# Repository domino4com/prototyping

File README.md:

# Prototype Boards

## Boards

| Board | Size | Design | Description |
|--|:--:|:--:|--|
| IPB | 1U |||
| IPP | 2x3U |||
| EPA | EXT || Analog sensor board |
| EPB | EXT || Bus board |

## Size
### Standard Boards
All standard boards are a multiple of 32x32 mm, called 1U (It comes from Lego, where one dot is 8x8mm).
In order to add two boards together, 0.1 mm is subtracted from each side (also a Lego standard).
So a single chip is 31.8x31.8 mm and a large 2x3 chip (2x3U) board is (2x32-0.1-0.1) x (3x32-0.1-0.1) 63.8x95.8mm
All boards are standard 1.6mm thick.
The rest you can deduct from the design.

### Extension boards (EXT)
No specific size requirements, but I try to keep the width within 31.8mm.
> NOTE: The boards are only 1mm thick!!!

## Eagle 
All boards are designed in Eagle, which you can [freely download](https://www.autodesk.com/products/eagle/free-download).

In Eagle there is an ULP, that allows you to make a library from the schematic/layout.

# License: 

Creative Commons Attribution-NonCommercial-ShareAlike 4.0 International Public License

[View License Deed](https://creativecommons.org/licenses/by-nc-sa/4.0/) | [View Legal Code](https://creativecommons.org/licenses/by-nc-sa/4.0/legalcode)

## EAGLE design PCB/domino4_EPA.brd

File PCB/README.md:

# Eagle files

## Boards

| Board | Size | Design | Description |
|--|:--:|:--:|--|
| IPB | 1U |||
| IPP | 2x3U |||
| EPA | EXT || Analog sensor board |
| EPB | EXT || Bus board |

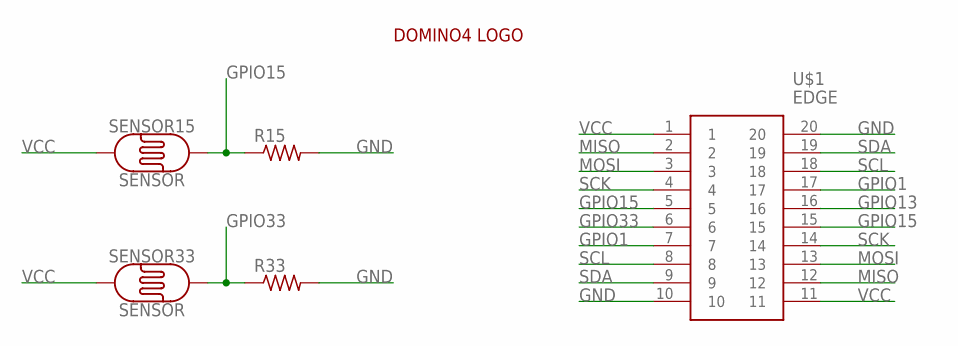
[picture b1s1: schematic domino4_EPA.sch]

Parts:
R15, R33: R-US_FLIPFLOP; 0805-THM
SENSOR15, SENSOR33: SENSOR; PHOTOCELL-KIT
U$1: EDGE
U$5: DOMINO4_LOGO

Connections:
GND: R15.2, R33.2, U$1.10, U$1.20
GPIO1: U$1.7, U$1.17
GPIO13: U$1.16
GPIO15: R15.1, SENSOR15.2, U$1.5, U$1.15
GPIO33: R33.1, SENSOR33.2, U$1.6
MISO: U$1.2, U$1.12
MOSI: U$1.3, U$1.13
SCK: U$1.4, U$1.14
SCL: U$1.8, U$1.18
SDA: U$1.9, U$1.19
VCC: SENSOR15.1, SENSOR33.1, U$1.1, U$1.11

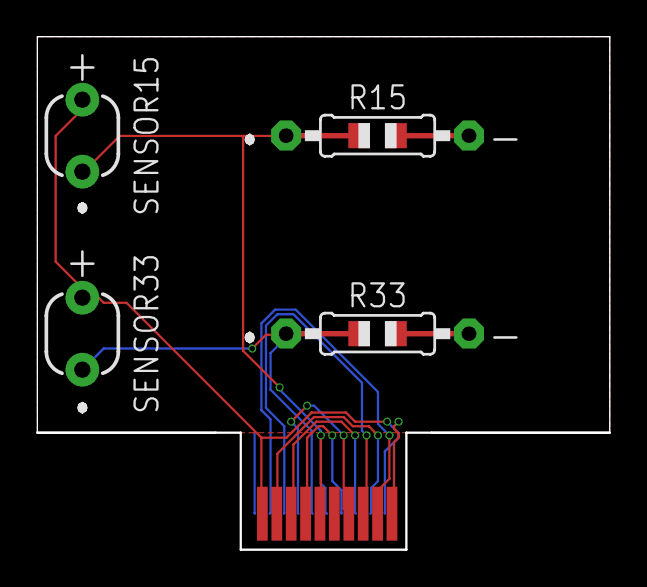
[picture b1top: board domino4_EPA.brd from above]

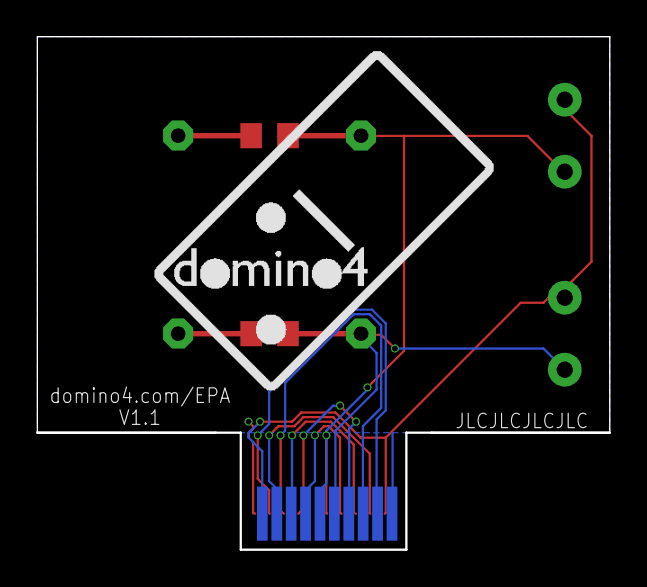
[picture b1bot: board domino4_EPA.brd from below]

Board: 2 copper layers, 31.8 x 28.5 mm, 7 parts (2 on the bottom side), 10 nets.

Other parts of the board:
U$3: JLCPCB-ORDER-NO

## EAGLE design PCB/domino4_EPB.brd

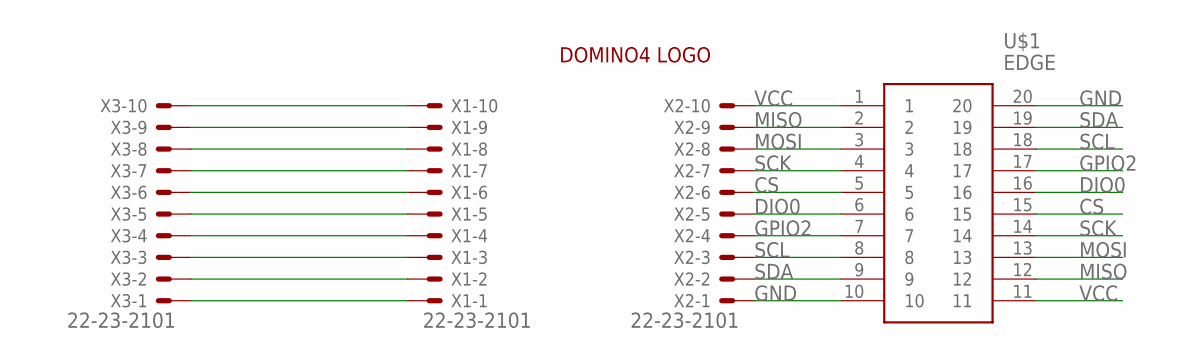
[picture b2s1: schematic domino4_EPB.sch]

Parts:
U$1: EDGE
U$2: DOMINO4_LOGO
X1, X2, X3: 22-23-2101

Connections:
CS: U$1.5, U$1.15, X2.6
DIO0: U$1.6, U$1.16, X2.5
GND: U$1.10, U$1.20, X2.1
GPIO2: U$1.7, U$1.17, X2.4
MISO: U$1.2, U$1.12, X2.9
MOSI: U$1.3, U$1.13, X2.8
unnamed: X1.10, X3.10
unnamed: X1.9, X3.9
unnamed: X1.8, X3.8
unnamed: X1.7, X3.7
unnamed: X1.6, X3.6
unnamed: X1.5, X3.5
unnamed: X1.4, X3.4
unnamed: X1.3, X3.3
unnamed: X1.2, X3.2
unnamed: X1.1, X3.1
SCK: U$1.4, U$1.14, X2.7
SCL: U$1.8, U$1.18, X2.3
SDA: U$1.9, U$1.19, X2.2
VCC: U$1.1, U$1.11, X2.10

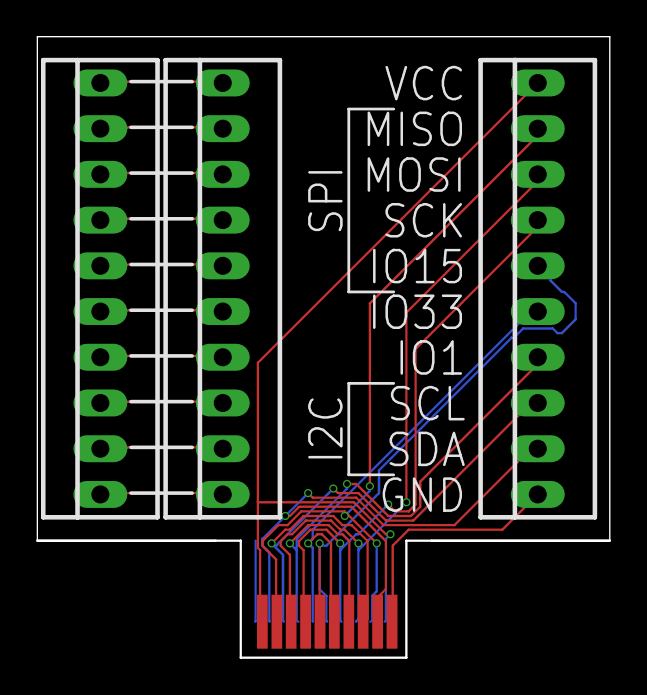
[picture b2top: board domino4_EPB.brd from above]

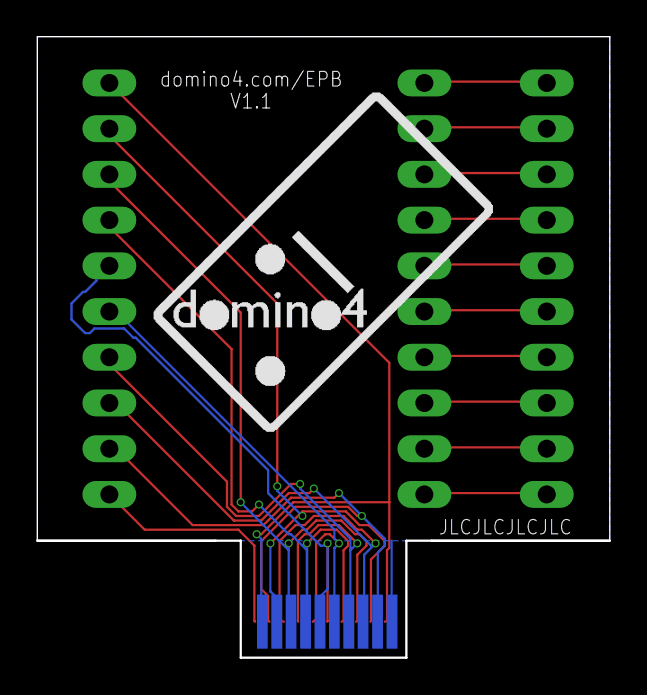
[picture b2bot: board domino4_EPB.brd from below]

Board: 2 copper layers, 31.8 x 34.5 mm, 6 parts (2 on the bottom side), 20 nets.

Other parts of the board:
U$3: JLCPCB-ORDER-NO

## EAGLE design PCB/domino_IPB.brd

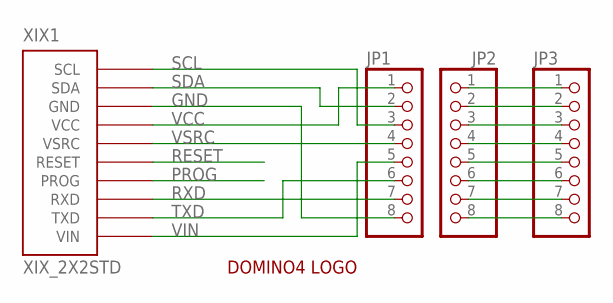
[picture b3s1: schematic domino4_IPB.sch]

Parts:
JP1, JP2, JP3: PINHD-1X8; 1X08
U$1: DOMINO4_LOGOHALF; DOMINO4_LOGO_HALF
XIX1: XIX_2X2STD; XIX_2X2

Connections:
GND: JP1.8, XIX1.GND@1 (GND), XIX1.GND@2 (GND), XIX1.GND@3 (GND), XIX1.GND@4 (GND)
unnamed: JP2.1, JP3.1
unnamed: JP2.2, JP3.2
unnamed: JP2.3, JP3.3
unnamed: JP2.4, JP3.4
unnamed: JP2.5, JP3.5
unnamed: JP2.6, JP3.6
unnamed: JP2.7, JP3.7
unnamed: JP2.8, JP3.8
PROG: XIX1.PROG@5 (PROG), XIX1.PROG@6 (PROG), XIX1.PROG@7 (PROG), XIX1.PROG@8 (PROG)
RESET: XIX1.RESET@5 (RESET), XIX1.RESET@6 (RESET), XIX1.RESET@7 (RESET), XIX1.RESET@8 (RESET)
RXD: JP1.7, XIX1.RXD@5 (RXD), XIX1.RXD@6 (RXD), XIX1.RXD@7 (RXD), XIX1.RXD@8 (RXD)
SCL: JP1.3, XIX1.SCL@1 (SCL), XIX1.SCL@2 (SCL), XIX1.SCL@3 (SCL), XIX1.SCL@4 (SCL)
SDA: JP1.2, XIX1.SDA@1 (SDA), XIX1.SDA@2 (SDA), XIX1.SDA@3 (SDA), XIX1.SDA@4 (SDA)
TXD: JP1.6, XIX1.TXD@5 (TXD), XIX1.TXD@6 (TXD), XIX1.TXD@7 (TXD), XIX1.TXD@8 (TXD)
VCC: JP1.1, XIX1.VCC@1 (VCC), XIX1.VCC@2 (VCC), XIX1.VCC@3 (VCC), XIX1.VCC@4 (VCC)
VIN: JP1.5, XIX1.VIN@5 (VIN), XIX1.VIN@6 (VIN), XIX1.VIN@7 (VIN), XIX1.VIN@8 (VIN)
VSRC: JP1.4, XIX1.VSRC@1 (VSRC), XIX1.VSRC@2 (VSRC), XIX1.VSRC@3 (VSRC), XIX1.VSRC@4 (VSRC)

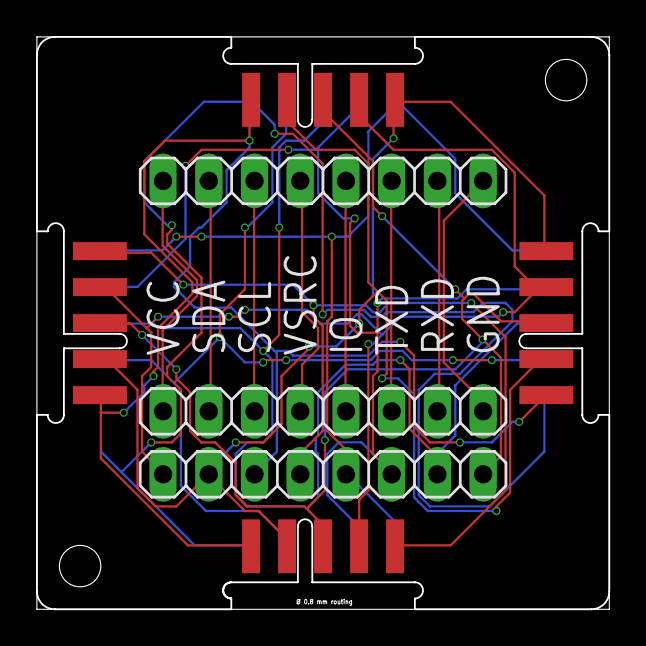
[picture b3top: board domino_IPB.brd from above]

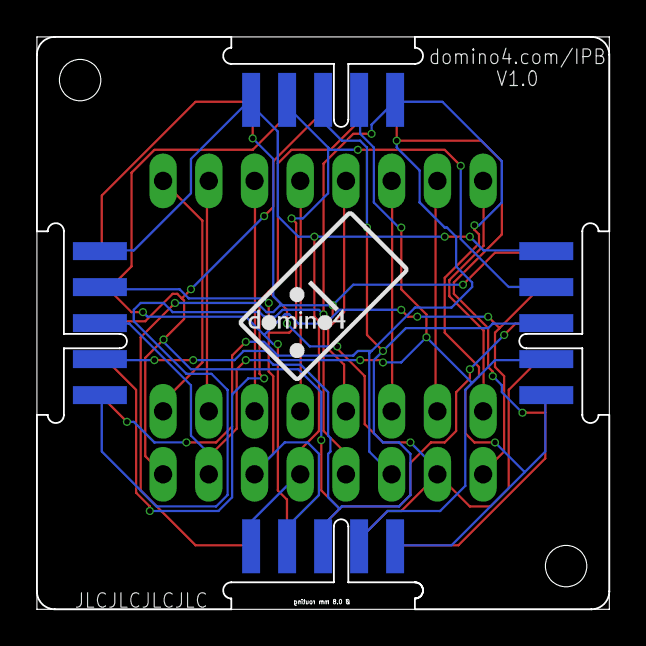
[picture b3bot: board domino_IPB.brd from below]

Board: 2 copper layers, 31.8 x 31.8 mm, 6 parts (2 on the bottom side), 18 nets.

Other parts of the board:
U$3: JLCPCB-ORDER-NO

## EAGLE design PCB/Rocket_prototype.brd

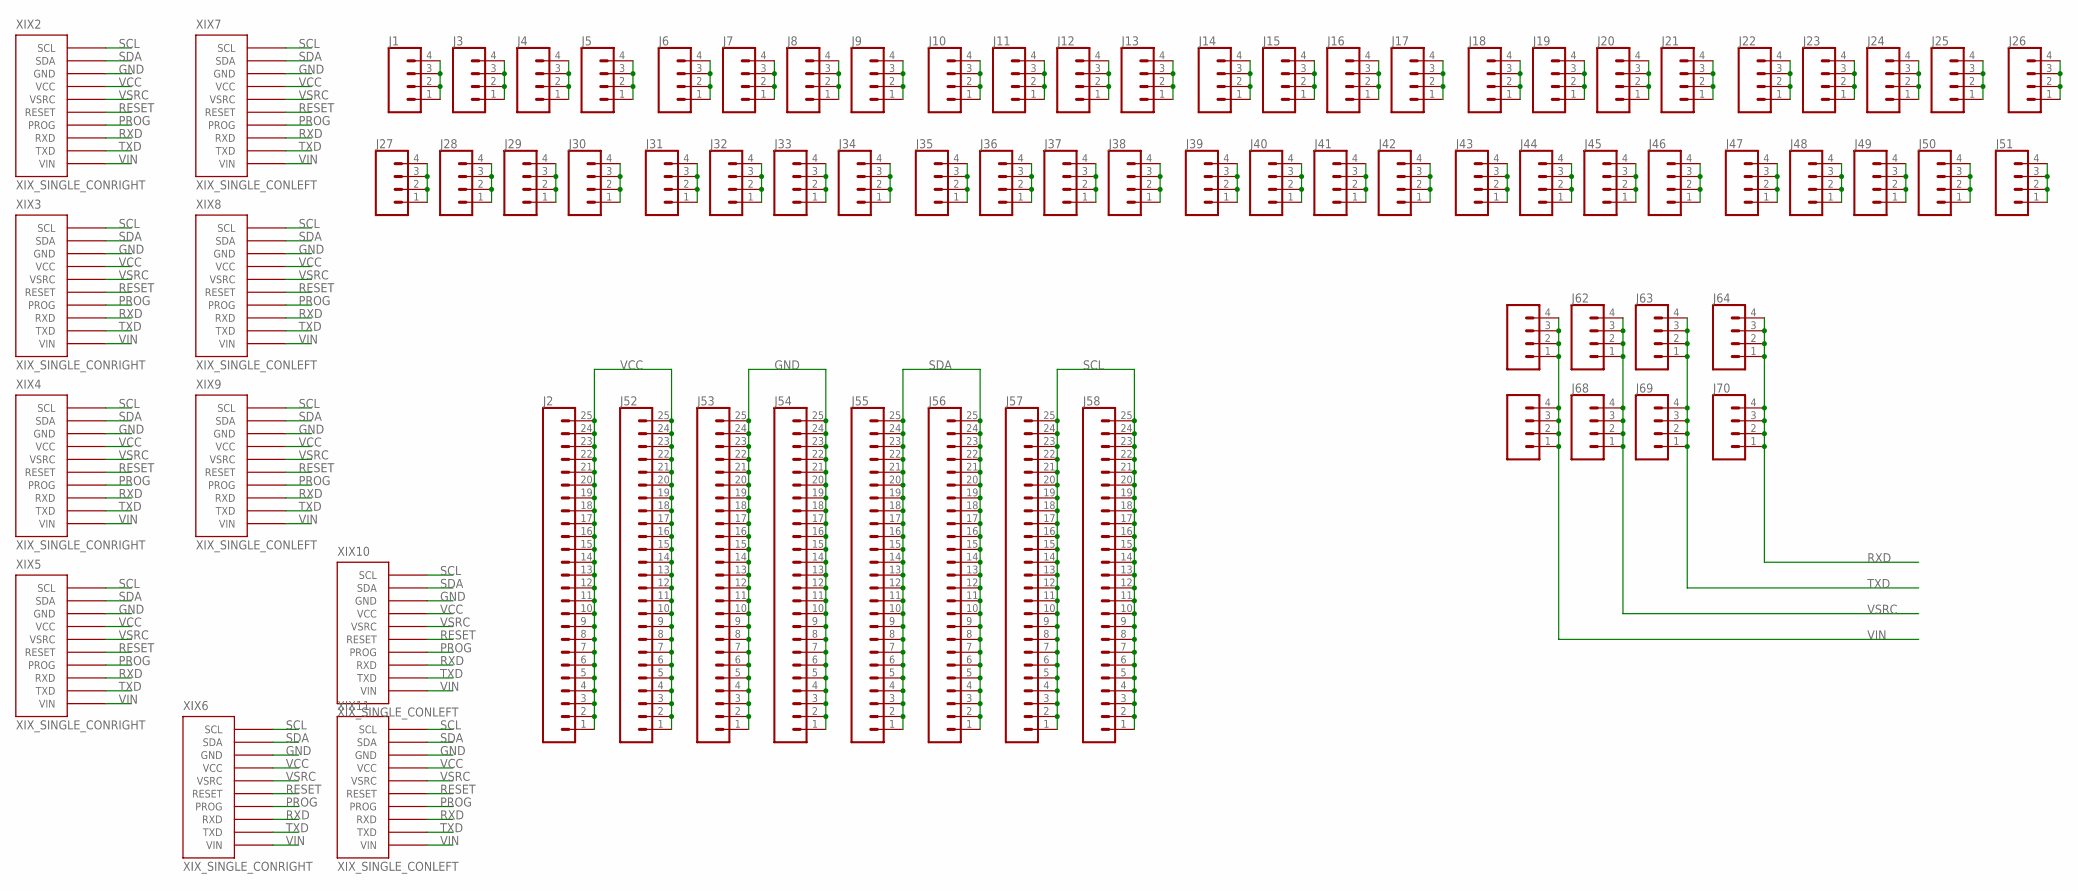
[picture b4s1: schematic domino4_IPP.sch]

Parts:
J1, J3, J4, J5, J6, J7, J8, J9, J10, J11, J12, J13, J14, J15, J16, J17, J18, J19, J20, J21, J22, J23, J24, J25, J26, J27, J28, J29, J30, J31, J32, J33, J34, J35, J36, J37, J38, J39, J40, J41, J42, J43, J44, J45, J46, J47, J48, J49, J50, J51, J61, J62, J63, J64, J67, J68, J69, J70: CONN_04PTH; 1X04
J2, J52, J53, J54, J55, J56, J57, J58: CONN_25; 1X25
XIX2, XIX3, XIX4, XIX5, XIX6: XIX_SINGLE_CONRIGHT; XIX_SINGLE_CON_RIGHT
XIX7, XIX8, XIX9, XIX10, XIX11: XIX_SINGLE_CONLEFT; XIX_SINGLE_CON_LEFT

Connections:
GND: J53.1, J53.2, J53.3, J53.4, J53.5, J53.6, J53.7, J53.8, J53.9, J53.10, J53.11, J53.12, J53.13, J53.14, J53.15, J53.16, J53.17, J53.18, J53.19, J53.20, J53.21, J53.22, J53.23, J53.24, J53.25, J54.1, J54.2, J54.3, J54.4, J54.5, J54.6, J54.7, J54.8, J54.9, J54.10, J54.11, J54.12, J54.13, J54.14, J54.15, J54.16, J54.17, J54.18, J54.19, J54.20, J54.21, J54.22, J54.23, J54.24, J54.25, XIX2.GND@4 (GND), XIX3.GND@4 (GND), XIX4.GND@4 (GND), XIX5.GND@4 (GND), XIX6.GND@4 (GND), XIX7.GND@1 (GND), XIX8.GND@1 (GND), XIX9.GND@1 (GND), XIX10.GND@1 (GND), XIX11.GND@1 (GND)
unnamed: J1.1, J1.2, J1.3, J1.4
unnamed: J3.1, J3.2, J3.3, J3.4
unnamed: J4.1, J4.2, J4.3, J4.4
unnamed: J5.1, J5.2, J5.3, J5.4
unnamed: J6.1, J6.2, J6.3, J6.4
unnamed: J7.1, J7.2, J7.3, J7.4
unnamed: J8.1, J8.2, J8.3, J8.4
unnamed: J9.1, J9.2, J9.3, J9.4
unnamed: J10.1, J10.2, J10.3, J10.4
unnamed: J11.1, J11.2, J11.3, J11.4
unnamed: J12.1, J12.2, J12.3, J12.4
unnamed: J13.1, J13.2, J13.3, J13.4
unnamed: J14.1, J14.2, J14.3, J14.4
unnamed: J15.1, J15.2, J15.3, J15.4
unnamed: J16.1, J16.2, J16.3, J16.4
unnamed: J17.1, J17.2, J17.3, J17.4
unnamed: J18.1, J18.2, J18.3, J18.4
unnamed: J19.1, J19.2, J19.3, J19.4
unnamed: J20.1, J20.2, J20.3, J20.4
unnamed: J21.1, J21.2, J21.3, J21.4
unnamed: J22.1, J22.2, J22.3, J22.4
unnamed: J23.1, J23.2, J23.3, J23.4
unnamed: J24.1, J24.2, J24.3, J24.4
unnamed: J25.1, J25.2, J25.3, J25.4
unnamed: J26.1, J26.2, J26.3, J26.4
unnamed: J27.1, J27.2, J27.3, J27.4
unnamed: J28.1, J28.2, J28.3, J28.4
unnamed: J29.1, J29.2, J29.3, J29.4
unnamed: J30.1, J30.2, J30.3, J30.4
unnamed: J31.1, J31.2, J31.3, J31.4
unnamed: J32.1, J32.2, J32.3, J32.4
unnamed: J33.1, J33.2, J33.3, J33.4
unnamed: J34.1, J34.2, J34.3, J34.4
unnamed: J35.1, J35.2, J35.3, J35.4
unnamed: J36.1, J36.2, J36.3, J36.4
unnamed: J37.1, J37.2, J37.3, J37.4
unnamed: J38.1, J38.2, J38.3, J38.4
unnamed: J39.1, J39.2, J39.3, J39.4
unnamed: J40.1, J40.2, J40.3, J40.4
unnamed: J41.1, J41.2, J41.3, J41.4
unnamed: J42.1, J42.2, J42.3, J42.4
unnamed: J43.1, J43.2, J43.3, J43.4
unnamed: J44.1, J44.2, J44.3, J44.4
unnamed: J45.1, J45.2, J45.3, J45.4
unnamed: J46.1, J46.2, J46.3, J46.4
unnamed: J47.1, J47.2, J47.3, J47.4
unnamed: J48.1, J48.2, J48.3, J48.4
unnamed: J49.1, J49.2, J49.3, J49.4
unnamed: J50.1, J50.2, J50.3, J50.4
unnamed: J51.1, J51.2, J51.3, J51.4
PROG: XIX2.PROG@8 (PROG), XIX3.PROG@8 (PROG), XIX4.PROG@8 (PROG), XIX5.PROG@8 (PROG), XIX6.PROG@8 (PROG), XIX7.PROG@2 (PROG), XIX8.PROG@2 (PROG), XIX9.PROG@2 (PROG), XIX10.PROG@2 (PROG), XIX11.PROG@2 (PROG)
RESET: XIX2.RESET@8 (RESET), XIX3.RESET@8 (RESET), XIX4.RESET@8 (RESET), XIX5.RESET@8 (RESET), XIX6.RESET@8 (RESET), XIX7.RESET@2 (RESET), XIX8.RESET@2 (RESET), XIX9.RESET@2 (RESET), XIX10.RESET@2 (RESET), XIX11.RESET@2 (RESET)
RXD: J64.1, J64.2, J64.3, J64.4, J70.1, J70.2, J70.3, J70.4, XIX2.RXD@8 (RXD), XIX3.RXD@8 (RXD), XIX4.RXD@8 (RXD), XIX5.RXD@8 (RXD), XIX6.RXD@8 (RXD), XIX7.RXD@2 (RXD), XIX8.RXD@2 (RXD), XIX9.RXD@2 (RXD), XIX10.RXD@2 (RXD), XIX11.RXD@2 (RXD)
SCL: J57.1, J57.2, J57.3, J57.4, J57.5, J57.6, J57.7, J57.8, J57.9, J57.10, J57.11, J57.12, J57.13, J57.14, J57.15, J57.16, J57.17, J57.18, J57.19, J57.20, J57.21, J57.22, J57.23, J57.24, J57.25, J58.1, J58.2, J58.3, J58.4, J58.5, J58.6, J58.7, J58.8, J58.9, J58.10, J58.11, J58.12, J58.13, J58.14, J58.15, J58.16, J58.17, J58.18, J58.19, J58.20, J58.21, J58.22, J58.23, J58.24, J58.25, XIX2.SCL@4 (SCL), XIX3.SCL@4 (SCL), XIX4.SCL@4 (SCL), XIX5.SCL@4 (SCL), XIX6.SCL@4 (SCL), XIX7.SCL@1 (SCL), XIX8.SCL@1 (SCL), XIX9.SCL@1 (SCL), XIX10.SCL@1 (SCL), XIX11.SCL@1 (SCL)
SDA: J55.1, J55.2, J55.3, J55.4, J55.5, J55.6, J55.7, J55.8, J55.9, J55.10, J55.11, J55.12, J55.13, J55.14, J55.15, J55.16, J55.17, J55.18, J55.19, J55.20, J55.21, J55.22, J55.23, J55.24, J55.25, J56.1, J56.2, J56.3, J56.4, J56.5, J56.6, J56.7, J56.8, J56.9, J56.10, J56.11, J56.12, J56.13, J56.14, J56.15, J56.16, J56.17, J56.18, J56.19, J56.20, J56.21, J56.22, J56.23, J56.24, J56.25, XIX2.SDA@4 (SDA), XIX3.SDA@4 (SDA), XIX4.SDA@4 (SDA), XIX5.SDA@4 (SDA), XIX6.SDA@4 (SDA), XIX7.SDA@1 (SDA), XIX8.SDA@1 (SDA), XIX9.SDA@1 (SDA), XIX10.SDA@1 (SDA), XIX11.SDA@1 (SDA)
TXD: J63.1, J63.2, J63.3, J63.4, J69.1, J69.2, J69.3, J69.4, XIX2.TXD@8 (TXD), XIX3.TXD@8 (TXD), XIX4.TXD@8 (TXD), XIX5.TXD@8 (TXD), XIX6.TXD@8 (TXD), XIX7.TXD@2 (TXD), XIX8.TXD@2 (TXD), XIX9.TXD@2 (TXD), XIX10.TXD@2 (TXD), XIX11.TXD@2 (TXD)
VCC: J2.1, J2.2, J2.3, J2.4, J2.5, J2.6, J2.7, J2.8, J2.9, J2.10, J2.11, J2.12, J2.13, J2.14, J2.15, J2.16, J2.17, J2.18, J2.19, J2.20, J2.21, J2.22, J2.23, J2.24, J2.25, J52.1, J52.2, J52.3, J52.4, J52.5, J52.6, J52.7, J52.8, J52.9, J52.10, J52.11, J52.12, J52.13, J52.14, J52.15, J52.16, J52.17, J52.18, J52.19, J52.20, J52.21, J52.22, J52.23, J52.24, J52.25, XIX2.VCC@4 (VCC), XIX3.VCC@4 (VCC), XIX4.VCC@4 (VCC), XIX5.VCC@4 (VCC), XIX6.VCC@4 (VCC), XIX7.VCC@1 (VCC), XIX8.VCC@1 (VCC), XIX9.VCC@1 (VCC), XIX10.VCC@1 (VCC), XIX11.VCC@1 (VCC)
VIN: J61.1, J61.2, J61.3, J61.4, J67.1, J67.2, J67.3, J67.4, XIX2.VRAW@8 (VIN), XIX3.VRAW@8 (VIN), XIX4.VRAW@8 (VIN), XIX5.VRAW@8 (VIN), XIX6.VRAW@8 (VIN), XIX7.VRAW@2 (VIN), XIX8.VRAW@2 (VIN), XIX9.VRAW@2 (VIN), XIX10.VRAW@2 (VIN), XIX11.VRAW@2 (VIN)
VSRC: J62.1, J62.2, J62.3, J62.4, J68.1, J68.2, J68.3, J68.4, XIX2.VBAT@4 (VSRC), XIX3.VBAT@4 (VSRC), XIX4.VBAT@4 (VSRC), XIX5.VBAT@4 (VSRC), XIX6.VBAT@4 (VSRC), XIX7.VBAT@1 (VSRC), XIX8.VBAT@1 (VSRC), XIX9.VBAT@1 (VSRC), XIX10.VBAT@1 (VSRC), XIX11.VBAT@1 (VSRC)

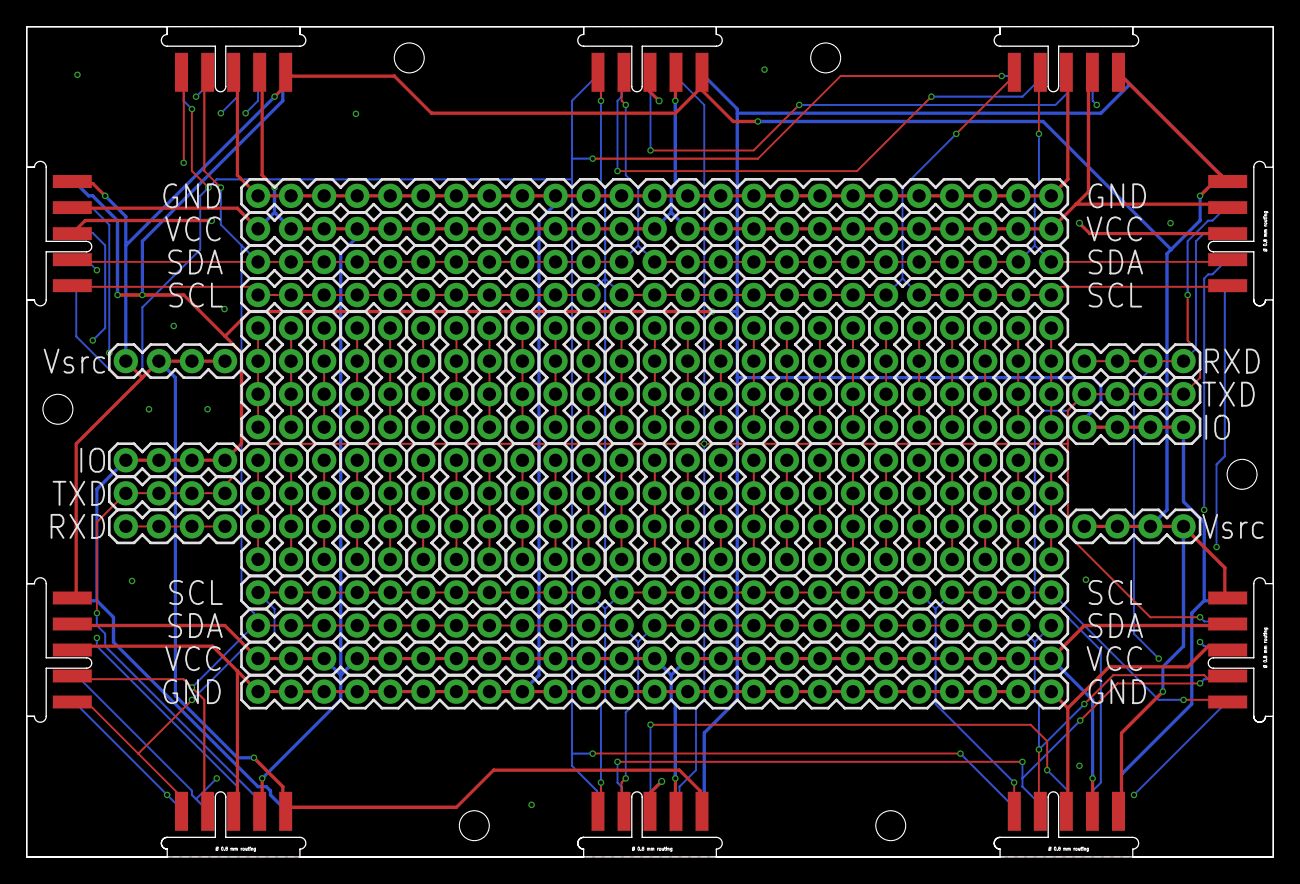
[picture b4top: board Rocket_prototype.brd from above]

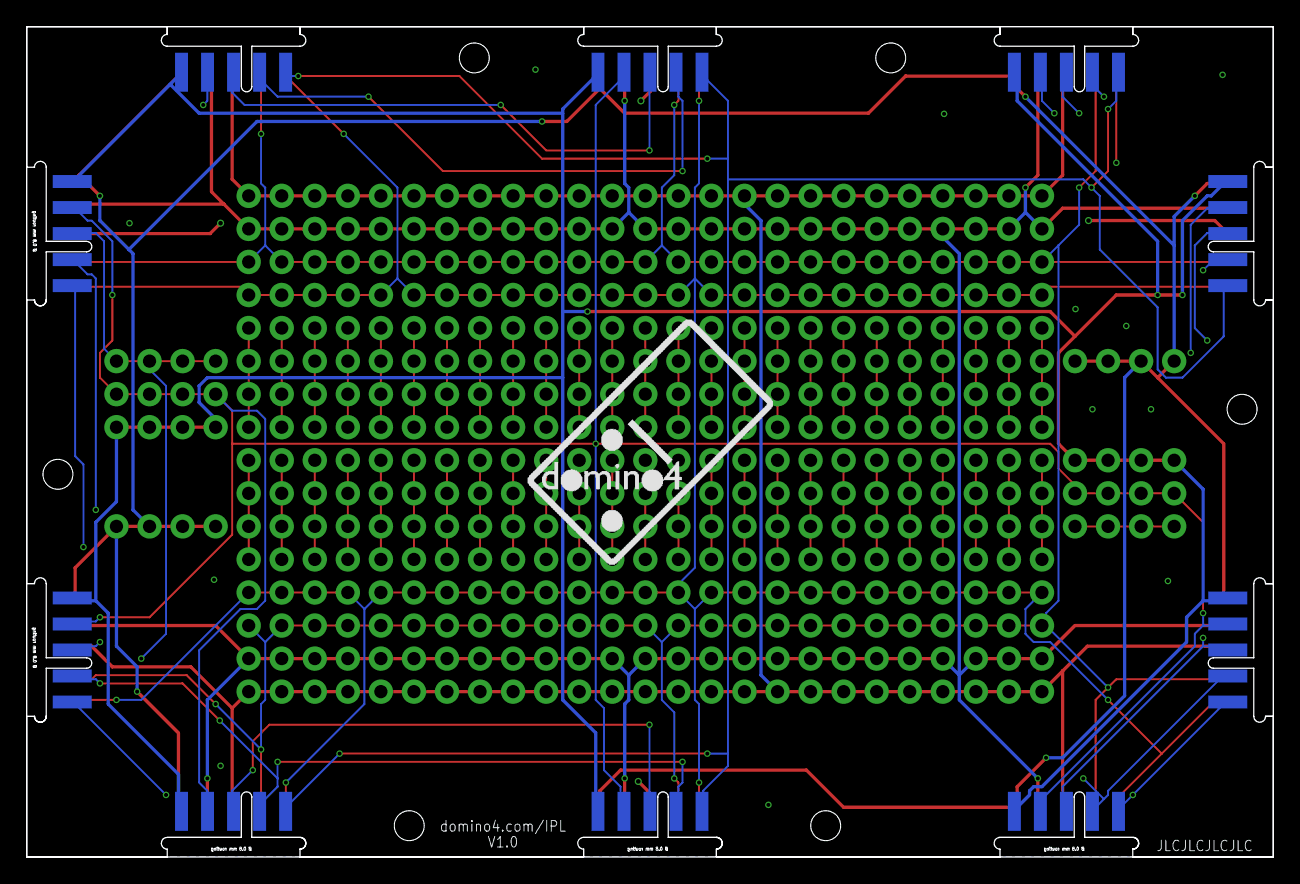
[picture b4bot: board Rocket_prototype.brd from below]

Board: 4 copper layers, 95.8 x 63.8 mm, 78 parts (2 on the bottom side), 60 nets.

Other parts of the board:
U$3: JLCPCB-ORDER-NO
U$5: DOMINO4_LOGO

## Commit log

2022-04-08 Rename readme.MD to README.md
2022-04-08 Rename domino_IPB_Bus.brd to domino_IPB.brd
2022-04-08 Rename domino_IPB_Bus.sch to domino4_IPB.sch
2022-04-08 Rename domino_IPB.brd to domino4_IPB.brd

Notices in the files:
parts and their libraries:
SparkFun-Connectors: Licensing: Creative Commons ShareAlike 4.0 International - https://creativecommons.org/licenses/by-sa/4.0
